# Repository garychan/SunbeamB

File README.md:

##Sunbeam rev B
==========

##What is it?
Sunbeam rev B is at90usb1287 based 5 axis reprap electronics.

## Licensing
==========
Creative Commons 
Attribution-NonCommercial-ShareAlike 3.0 Unported (CC BY-NC-SA 3.0)

Copyright (C) 2012 Arkadiusz Spiewak (Wulfnor)

##Author
Author is: Arkadiusz Spiewak a'ka Wulfnor

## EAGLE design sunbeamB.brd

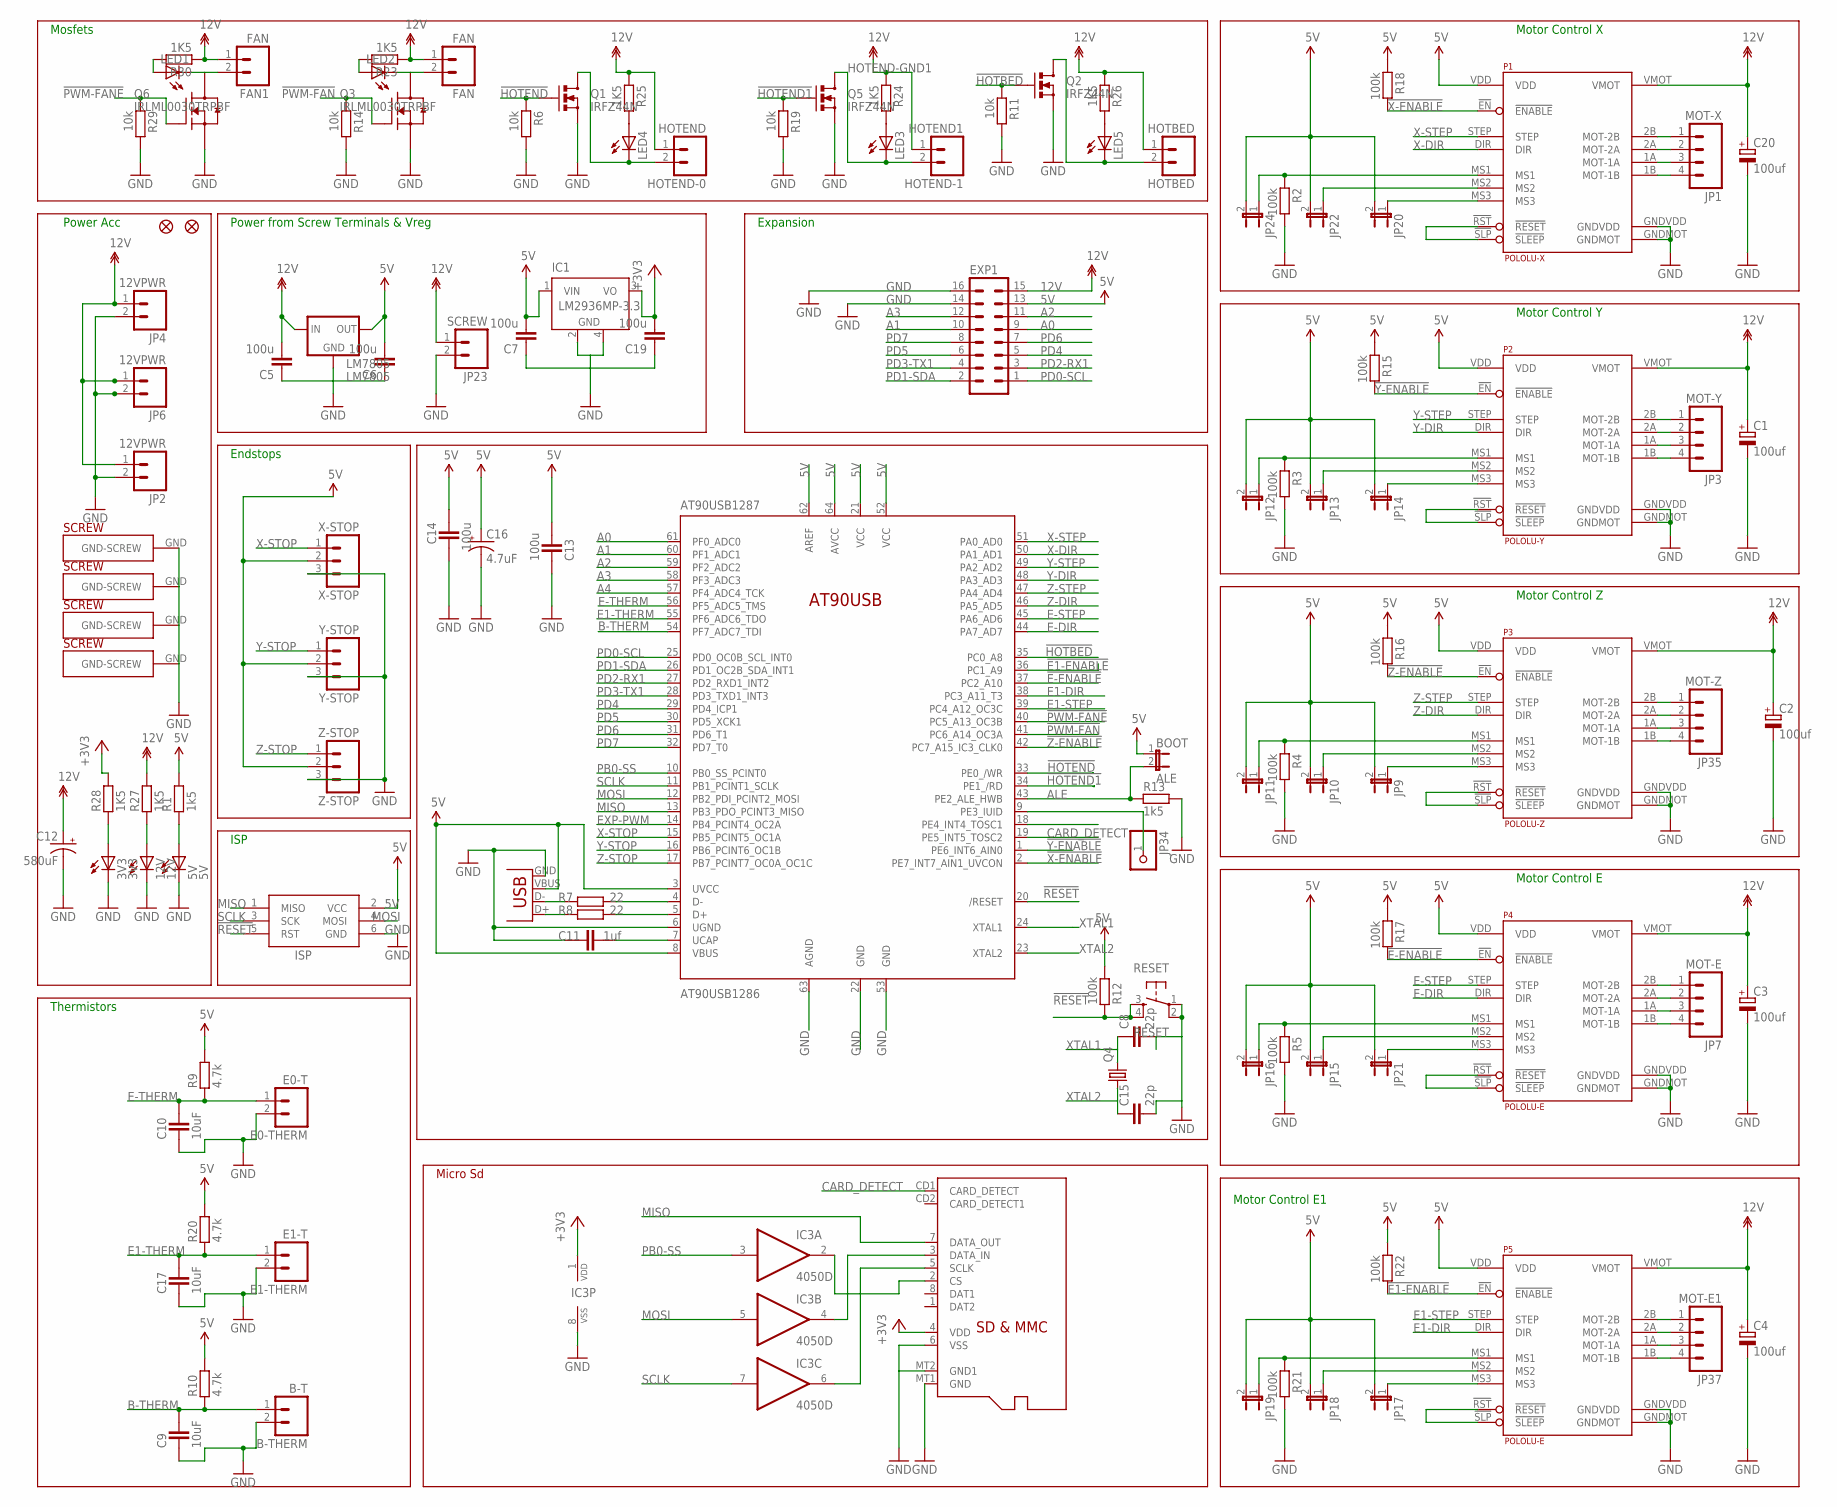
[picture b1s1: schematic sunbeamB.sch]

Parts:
3V3: 3V3; CHIPLED_0805
5V: 5V; CHIPLED_0805
12V: 12V; CHIPLED_0805
AT90USB1287: AT90USB1286; TQFP64-2
B-THERM: B-T; MOLEX-1X2
BOOT: ALE; 1X02
C1, C2, C3, C4, C20: 100uf; UD-6,3X7,7_NICHICON
C5, C6, C7, C19: 100u; C0805
C8, C15: 22p; C0805
C9, C10, C17: 10uF; CAPC2012X145AN
C11: 1uf; CAPC2012X145AN
C12: 580uF; CPOL-RADIAL-1000UF-25V
C13, C14: 100u; CAPC2012X145AN
C16: 4.7uF; CPOL-RADIAL-10UF-25V
E0-THERM: E0-T; MOLEX-1X2
E1-THERM: E1-T; MOLEX-1X2
EXP1: MA08-2
FAN, FAN1: FAN; MOLEX-1X2
HOTBED: HOTBED; SCREWTERMINAL-5MM-2
HOTEND-0: HOTEND; SCREWTERMINAL-5MM-2
HOTEND-1: HOTEND1; SCREWTERMINAL-5MM-2
IC1: LM2936MP-3.3; SOT223
IC3: 4050D; SO16
ISP: ISP; AVRISP
J1: USB; USB-B-PTH
JP1: MOT-X; MOLEX-1X4
JP2, JP4, JP6: 12VPWR; MOLEX-1X2
JP3: MOT-Y; MOLEX-1X4
JP5, JP8: FIDUCIAL1X2.5; FIDUCIAL-1X2.5
JP7: MOT-E; MOLEX-1X4
JP9, JP10, JP11, JP12, JP13, JP14, JP15, JP16, JP17, JP18, JP19, JP20, JP21, JP22, JP24: JUMPER-2-OLDSMD-NO; SJ_2S-NO
JP23: SCREW; SCREWTERMINAL-5MM-2
JP34: PINHD-1X1; 1X01
JP35: MOT-Z; MOLEX-1X4
JP37: MOT-E1; MOLEX-1X4
LED1, LED2, LED3, LED4, LED5: LEDCHIPLED_0805; CHIPLED_0805
LM7805: LM7805; 78XXL-CUSTOM
MICRO-SD: MICROSD
P1: POLOLU-X; POLOLU-ALLEGRO-PTH
P2: POLOLU-Y; POLOLU-ALLEGRO-PTH
P3: POLOLU-Z; POLOLU-ALLEGRO-PTH
P4, P5: POLOLU-E; POLOLU-ALLEGRO-PTH
Q1, Q2, Q5: IRFZ44N; TO220V
Q3, Q6: IRLML0030TRPBF; SOT95P280X135-3N
Q4: CRYSTALHC49UP; HC49UP
R1, R13: 1k5; RESC2012X70N
R2, R3, R4, R5, R12, R15, R16, R17, R18, R21, R22: 100k; RESC2012X70N
R6, R11, R14, R19, R29: 10k; RESC2012X70N
R7, R8: 22; RESC2012X70N
R9, R10, R20: 4.7k; RESC2012X70N
R23, R24, R25, R26, R27, R28, R30: 1K5; RESC2012X70N
RESET: RESET; TACTILE-PTH
U$47, U$48, U$49, U$50: PLATED-SCREW; PLATEDSCREW
X-STOP: X-STOP; MOLEX-1X3
Y-STOP: Y-STOP; MOLEX-1X3
Z-STOP: Z-STOP; MOLEX-1X3

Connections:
5V: AT90USB1287.3 (UVCC), AT90USB1287.8 (VBUS), AT90USB1287.21 (VCC), AT90USB1287.52 (VCC), AT90USB1287.62 (AREF), AT90USB1287.64 (AVCC), BOOT.1, C6.2, C7.2, C13.2, C14.1, C16.1 (+), EXP1.13, IC1.1 (VIN), ISP.2 (VCC), J1.VBUS, JP9.2, JP10.2, JP11.2, JP12.2, JP13.2, JP14.2, JP15.2, JP16.2, JP17.2, JP18.2, JP19.2, JP20.2, JP21.2, JP22.2, JP24.2, LM7805.OUT, P1.VDD, P2.VDD, P3.VDD, P4.VDD, P5.VDD, R1.2, R9.2, R10.2, R12.2, R15.1, R16.1, R17.1, R18.1, R20.2, R22.1, X-STOP.2, Y-STOP.2, Z-STOP.2
12V: C1.+, C2.+, C3.+, C4.+, C5.2, C12.1 (+), C20.+, EXP1.15, FAN.1, FAN1.1, HOTBED.1, HOTEND-0.1, HOTEND-1.1, JP2.1, JP4.1, JP6.1, JP23.1, LM7805.IN, P1.VMOT, P2.VMOT, P3.VMOT, P4.VMOT, P5.VMOT, R23.1, R24.1, R25.1, R26.1, R27.2, R30.1
!E1-ENABLE: AT90USB1287.36 (PC1_A9), P5.!EN (!ENABLE), R22.2
!E-ENABLE: AT90USB1287.37 (PC2_A10), P4.!EN (!ENABLE), R17.2
!HOTBED: AT90USB1287.35 (PC0_A8), Q2.1 (G), R11.1
!HOTEND: AT90USB1287.33 (PE0_/WR), Q1.1 (G), R6.1
!HOTEND1: AT90USB1287.34 (PE1_/RD), Q5.1 (G), R19.1
!PWM-FAN: AT90USB1287.41 (PC6_A14_OC3A), Q3.1 (G), R14.1
!PWM-FANE: AT90USB1287.40 (PC5_A13_OC3B), Q6.1 (G), R29.1
!RESET: AT90USB1287.20 (/RESET), ISP.5 (RST), R12.1, RESET.3, RESET.4
!X-ENABLE: AT90USB1287.2 (PE7_INT7_AIN1_UVCON), P1.!EN (!ENABLE), R18.2
!Y-ENABLE: AT90USB1287.1 (PE6_INT6_AIN0), P2.!EN (!ENABLE), R15.2
!Z-ENABLE: AT90USB1287.42 (PC7_A15_IC3_CLK0), P3.!EN (!ENABLE), R16.2
+3V3: C19.2, IC1.3 (VO), IC3.1 (VDD), MICRO-SD.4 (VDD), R28.2
A0: AT90USB1287.61 (PF0_ADC0), EXP1.9
A1: AT90USB1287.60 (PF1_ADC1), EXP1.10
A2: AT90USB1287.59 (PF2_ADC2), EXP1.11
A3: AT90USB1287.58 (PF3_ADC3), EXP1.12
A4: AT90USB1287.57 (PF4_ADC4_TCK)
ALE: AT90USB1287.43 (PE2_ALE_HWB), BOOT.2, R13.1
B-THERM: AT90USB1287.54 (PF7_ADC7_TDI), B-THERM.1, C9.2, R10.1
CARD_DETECT: AT90USB1287.19 (PE5_INT5_TOSC2), MICRO-SD.CD1 (CARD_DETECT)
E1-DIR: AT90USB1287.38 (PC3_A11_T3), P5.DIR
E1-STEP: AT90USB1287.39 (PC4_A12_OC3C), P5.STEP
E1-THERM: AT90USB1287.55 (PF6_ADC6_TDO), C17.2, E1-THERM.1, R20.1
E-DIR: AT90USB1287.44 (PA7_AD7), P4.DIR
E-MOT-1A: JP7.3, P4.1A (MOT-1A)
E-MOT-1A1: JP37.3, P5.1A (MOT-1A)
E-MOT-1B: JP7.4, P4.1B (MOT-1B)
E-MOT-1B1: JP37.4, P5.1B (MOT-1B)
E-MOT-2A: JP7.2, P4.2A (MOT-2A)
E-MOT-2A1: JP37.2, P5.2A (MOT-2A)
E-MOT-2B: JP7.1, P4.2B (MOT-2B)
E-MOT-2B1: JP37.1, P5.2B (MOT-2B)
E-MS1: JP16.1, P4.MS1, R5.1
E-MS2: JP15.1, P4.MS2
E-MS3: JP21.1, P4.MS3
E-MS4: JP19.1, P5.MS1, R21.1
E-MS5: JP18.1, P5.MS2
E-MS6: JP17.1, P5.MS3
E-RESETSLEEP: P4.!RST (!RESET), P4.!SLP (!SLEEP)
E-RESETSLEEP1: P5.!RST (!RESET), P5.!SLP (!SLEEP)
E-STEP: AT90USB1287.45 (PA6_AD6), P4.STEP
E-THERM: AT90USB1287.56 (PF5_ADC5_TMS), C10.2, E0-THERM.1, R9.1
EXP-PWM: AT90USB1287.14 (PB4_PCINT4_OC2A)
GND: 3V3.C, 5V.C, 12V.C, AT90USB1287.6 (UGND), AT90USB1287.22 (GND), AT90USB1287.53 (GND), AT90USB1287.63 (AGND), B-THERM.2, C1.-, C2.-, C3.-, C4.-, C5.1, C6.1, C7.1, C8.2, C9.1, C10.1, C11.1, C12.2 (-), C13.1, C14.2, C15.2, C16.2 (-), C17.1, C19.1, C20.-, E0-THERM.2, E1-THERM.2, EXP1.14, EXP1.16, IC1.2 (GND), IC1.4 (GND), IC3.8 (VSS), ISP.6 (GND), J1.GND, JP2.2, JP4.2, JP6.2, JP23.2, LM7805.GND, MICRO-SD.6 (VSS), MICRO-SD.MT1 (GND), MICRO-SD.MT2 (GND1), P1.GNDMOT, P1.GNDVDD, P2.GNDMOT, P2.GNDVDD, P3.GNDMOT, P3.GNDVDD, P4.GNDMOT, P4.GNDVDD, P5.GNDMOT, P5.GNDVDD, Q1.3 (S), Q2.3 (S), Q3.2 (S), Q5.3 (S), Q6.2 (S), R2.2, R3.2, R4.2, R5.2, R6.2, R11.2, R13.2, R14.2, R19.2, R21.2, R29.2, RESET.1, RESET.2, U$47.GND, U$48.GND, U$49.GND, U$50.GND, X-STOP.3, Y-STOP.3, Z-STOP.3
HOTBED-GND: HOTBED.2, LED5.C, Q2.2 (D)
HOTEND-GND: HOTEND-0.2, LED4.C, Q1.2 (D)
HOTEND-GND1: HOTEND-1.2, LED3.C, Q5.2 (D)
MISO: AT90USB1287.13 (PB3_PDO_PCINT3_MISO), ISP.1 (MISO), MICRO-SD.7 (DATA_OUT)
MOSI: AT90USB1287.12 (PB2_PDI_PCINT2_MOSI), IC3.5 (I), ISP.4 (MOSI)
unnamed: 5V.A, R1.1
unnamed: J1.D-, R7.1
unnamed: AT90USB1287.4 (D-), R7.2
unnamed: AT90USB1287.5 (D+), R8.2
unnamed: J1.D+, R8.1
unnamed: FAN.2, LED2.C, Q3.3 (D)
unnamed: AT90USB1287.9 (PE3_IUID), JP34.1
unnamed: LED2.A, R23.2
unnamed: AT90USB1287.7 (UCAP), C11.2
unnamed: 3V3.A, R28.1
unnamed: LED4.A, R25.2
unnamed: LED3.A, R24.2
unnamed: LED5.A, R26.2
unnamed: 12V.A, R27.1
unnamed: IC3.6 (O), MICRO-SD.5 (SCLK)
unnamed: IC3.4 (O), MICRO-SD.3 (DATA_IN)
unnamed: IC3.2 (O), MICRO-SD.2 (CS)
unnamed: FAN1.2, LED1.C, Q6.3 (D)
unnamed: LED1.A, R30.2
PB0-SS: AT90USB1287.10 (PB0_SS_PCINT0), IC3.3 (I)
PD0-SCL: AT90USB1287.25 (PD0_OC0B_SCL_INT0), EXP1.1
PD1-SDA: AT90USB1287.26 (PD1_OC2B_SDA_INT1), EXP1.2
PD2-RX1: AT90USB1287.27 (PD2_RXD1_INT2), EXP1.3
PD3-TX1: AT90USB1287.28 (PD3_TXD1_INT3), EXP1.4
PD4: AT90USB1287.29 (PD4_ICP1), EXP1.5
PD5: AT90USB1287.30 (PD5_XCK1), EXP1.6
PD6: AT90USB1287.31 (PD6_T1), EXP1.7
PD7: AT90USB1287.32 (PD7_T0), EXP1.8
SCLK: AT90USB1287.11 (PB1_PCINT1_SCLK), IC3.7 (I), ISP.3 (SCK)
X-DIR: AT90USB1287.50 (PA1_AD1), P1.DIR
X-MOT-1A: JP1.3, P1.1A (MOT-1A)
X-MOT-1B: JP1.4, P1.1B (MOT-1B)
X-MOT-2A: JP1.2, P1.2A (MOT-2A)
X-MOT-2B: JP1.1, P1.2B (MOT-2B)
X-MS1: JP24.1, P1.MS1, R2.1
X-MS2: JP22.1, P1.MS2
X-MS3: JP20.1, P1.MS3
X-RESETSLEEP: P1.!RST (!RESET), P1.!SLP (!SLEEP)
X-STEP: AT90USB1287.51 (PA0_AD0), P1.STEP
X-STOP: AT90USB1287.15 (PB5_PCINT5_OC1A), X-STOP.1
XTAL1: AT90USB1287.24 (XTAL1), C8.1, Q4.2
XTAL2: AT90USB1287.23 (XTAL2), C15.1, Q4.1
Y-DIR: AT90USB1287.48 (PA3_AD3), P2.DIR
Y-MOT-1A: JP3.3, P2.1A (MOT-1A)
Y-MOT-1B: JP3.4, P2.1B (MOT-1B)
Y-MOT-2A: JP3.2, P2.2A (MOT-2A)
Y-MOT-2B: JP3.1, P2.2B (MOT-2B)
Y-MS1: JP12.1, P2.MS1, R3.1
Y-MS2: JP13.1, P2.MS2
Y-MS3: JP14.1, P2.MS3
Y-RESETSLEEP: P2.!RST (!RESET), P2.!SLP (!SLEEP)
Y-STEP: AT90USB1287.49 (PA2_AD2), P2.STEP
Y-STOP: AT90USB1287.16 (PB6_PCINT6_OC1B), Y-STOP.1
Z-DIR: AT90USB1287.46 (PA5_AD5), P3.DIR
Z-MOT-1A: JP35.3, P3.1A (MOT-1A)
Z-MOT-1B: JP35.4, P3.1B (MOT-1B)
Z-MOT-2A: JP35.2, P3.2A (MOT-2A)
Z-MOT-2B: JP35.1, P3.2B (MOT-2B)
Z-MS1: JP11.1, P3.MS1, R4.1
Z-MS2: JP10.1, P3.MS2
Z-MS3: JP9.1, P3.MS3
Z-RESETSLEEP: P3.!RST (!RESET), P3.!SLP (!SLEEP)
Z-STEP: AT90USB1287.47 (PA4_AD4), P3.STEP
Z-STOP: AT90USB1287.17 (PB7_PCINT7_OC0A_OC1C), Z-STOP.1

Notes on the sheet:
Motor Control X
Motor Control Y
Motor Control Z
Motor Control E
Thermistors
Endstops
Mosfets
Power Acc
Power from Screw Terminals & Vreg
Motor Control E1
Expansion
Micro Sd
ISP

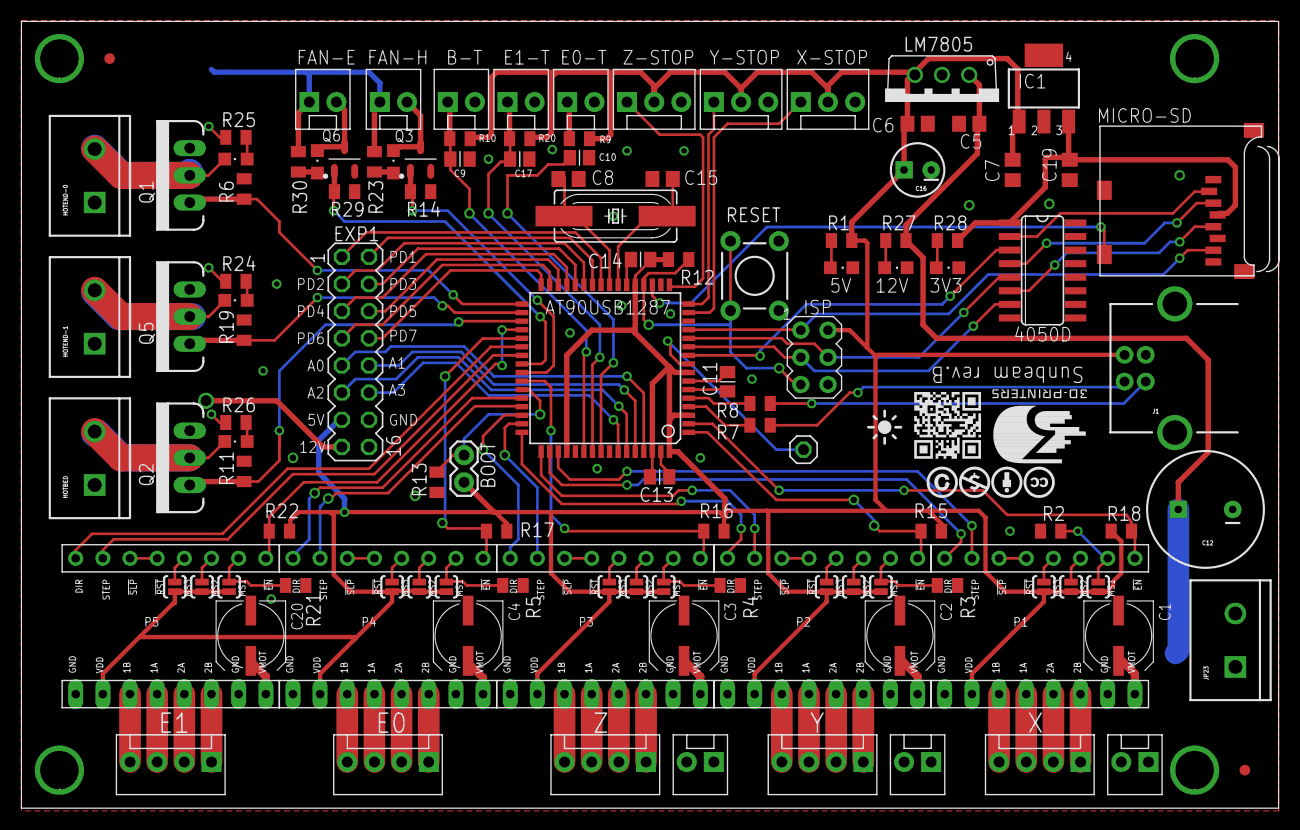
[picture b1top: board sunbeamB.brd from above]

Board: 2 copper layers, 117.6 x 73.6 mm, 120 parts (0 on the bottom side), 113 nets.

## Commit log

2013-02-24 added readme file
